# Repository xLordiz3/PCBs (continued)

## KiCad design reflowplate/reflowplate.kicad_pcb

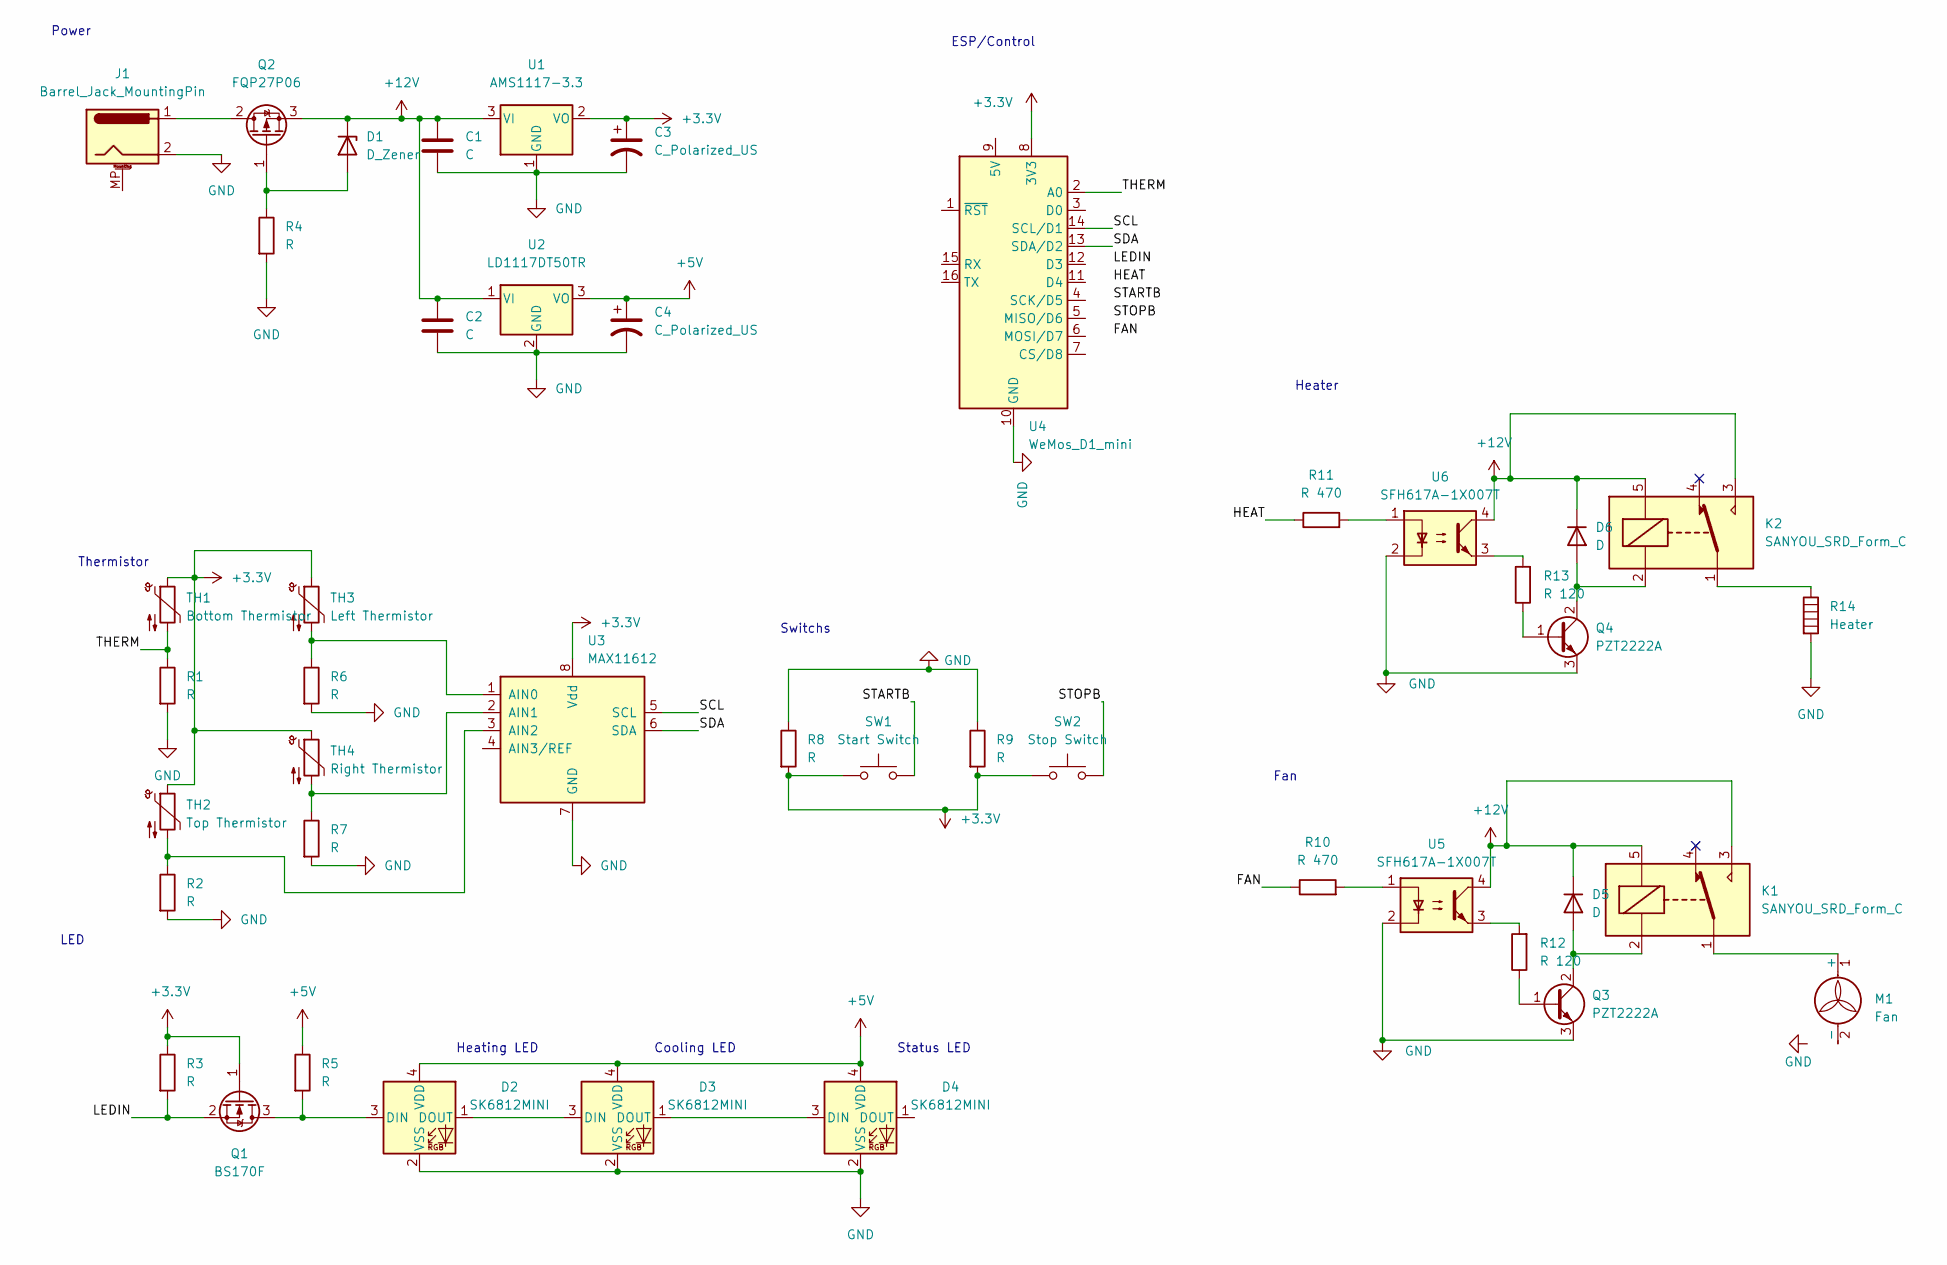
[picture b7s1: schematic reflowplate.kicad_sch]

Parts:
C1, C2: C; CP_EIA-6032-15_Kemet-U_Pad2.25x2.35mm_HandSolder
C3, C4: C_Polarized_US; CP_Elec_5x5.7
D1: D_Zener; D_0805_2012Metric_Pad1.15x1.40mm_HandSolder
D2, D3, D4: SK6812MINI; LED_SK6812MINI_PLCC4_3.5x3.5mm_P1.75mm
D5, D6: D; D_0805_2012Metric_Pad1.15x1.40mm_HandSolder
J1: Barrel_Jack_MountingPin; BarrelJack_Horizontal
K1, K2: SANYOU_SRD_Form_C; Relay_SPDT_SANYOU_SRD_Series_Form_C
M1: Fan; TerminalBlock_Wuerth_691311400102_P7.62mm
Q1: BS170F; SOT-23
Q2: FQP27P06; TO-252-3_TabPin2
Q3, Q4: PZT2222A; SOT-223-3_TabPin2
R1, R2, R3, R4, R5, R6, R7, R8, R9: R; R_0805_2012Metric_Pad1.20x1.40mm_HandSolder
R10, R11: R 470; R_0805_2012Metric_Pad1.20x1.40mm_HandSolder
R12, R13: R 120; R_0805_2012Metric_Pad1.20x1.40mm_HandSolder
R14: Heater; TerminalBlock_Wuerth_691311400102_P7.62mm
SW1: Start Switch; SW_Push_1P1T_NO_6x6mm_H9.5mm
SW2: Stop Switch; SW_Push_1P1T_NO_6x6mm_H9.5mm
TH1: Bottom Thermistor; PinHeader_1x02_P2.54mm_Vertical
TH2: Top Thermistor; PinHeader_1x02_P2.54mm_Vertical
TH3: Left Thermistor; PinHeader_1x02_P2.54mm_Vertical
TH4: Right Thermistor; PinHeader_1x02_P2.54mm_Vertical
U1: AMS1117-3.3; SOT-223-3_TabPin2
U2: LD1117DT50TR; TO-252-2
U3: MAX11612; MSOP-8+SOT23-8
U4: WeMos_D1_mini; WEMOS_D1_mini_light
U5, U6: SFH617A-1X007T; SMDIP-4_W9.53mm_Clearance8mm

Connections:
+3.3V: C3.1, Q1.1 (G), R3.1, R8.2, R9.2, SW1.1, SW2.1, TH1.1, TH2.1, TH3.1, TH4.1, U1.2 (VO), U3.8 (Vdd), U4.8 (3V3)
+5V: C4.1, D2.4 (VDD), D3.4 (VDD), D4.4 (VDD), R5.1, U2.3 (VO)
+12V: C1.1, C2.1, D1.1 (K), D5.1 (K), D6.1 (K), K1.3, K1.5, K2.3, K2.5, Q2.3 (S), U1.3 (VI), U2.1 (VI), U5.4, U6.4
/FAN: R10.1
/HEAT: R11.1
/LEDIN: Q1.2 (S), R3.2
/SCL: U3.5 (SCL), U4.14 (SCL/D1)
/SDA: U3.6 (SDA), U4.13 (SDA/D2)
/STARTB: SW1.2
/STOPB: SW2.2
/THERM: R1.1, TH1.2, U4.2 (A0)
GND: C1.2, C2.2, C3.2, C4.2, D2.2 (VSS), D3.2 (VSS), D4.2 (VSS), J1.2, M1.2 (-), Q3.3 (E), Q4.3 (E), R1.2, R2.2, R4.2, R6.2, R7.2, R8.1, R9.1, R14.2, U1.1 (GND), U2.2 (GND), U3.7 (GND), U4.10 (GND), U5.2, U6.2
unnamed: D1.2 (A), Q2.1 (G), R4.1
unnamed: D2.1 (DOUT), D3.3 (DIN)
unnamed: D2.3 (DIN), Q1.3 (D), R5.2
unnamed: D3.1 (DOUT), D4.3 (DIN)
unnamed: D5.2 (A), K1.2, Q3.2 (C)
unnamed: D6.2 (A), K2.2, Q4.2 (C)
unnamed: J1.1, Q2.2 (D)
unnamed: K1.1, M1.1 (+)
unnamed: K2.1, R14.1
unnamed: Q3.1 (B), R12.1
unnamed: Q4.1 (B), R13.1
unnamed: R2.1, TH2.2, U3.3 (AIN2)
unnamed: R6.1, TH3.2, U3.1 (AIN0)
unnamed: R7.1, TH4.2, U3.2 (AIN1)
unnamed: R10.2, U5.1
unnamed: R11.2, U6.1
unnamed: R12.2, U5.3
unnamed: R13.2, U6.3

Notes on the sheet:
Cooling LED
Switchs
Fan
Status LED
Heating LED
ESP/Control
Heater
LED
Thermistor
Power

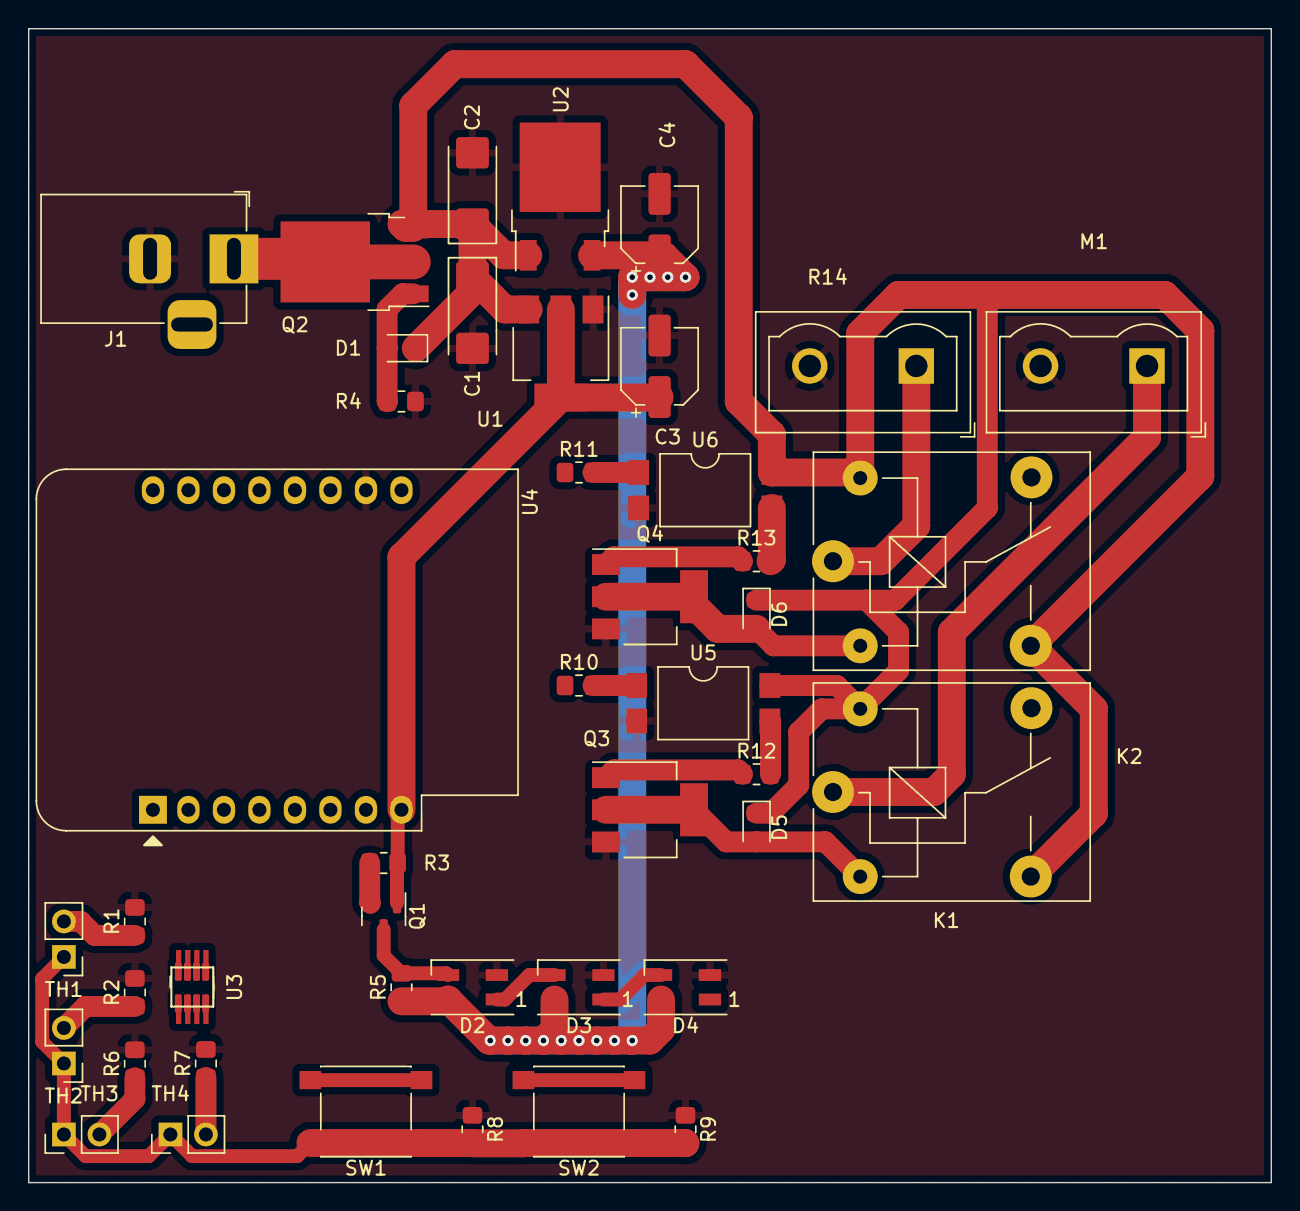
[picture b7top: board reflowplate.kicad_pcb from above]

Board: 2 copper layers, 88.9 x 82.5 mm, 44 parts (0 on the bottom side), 26 nets.

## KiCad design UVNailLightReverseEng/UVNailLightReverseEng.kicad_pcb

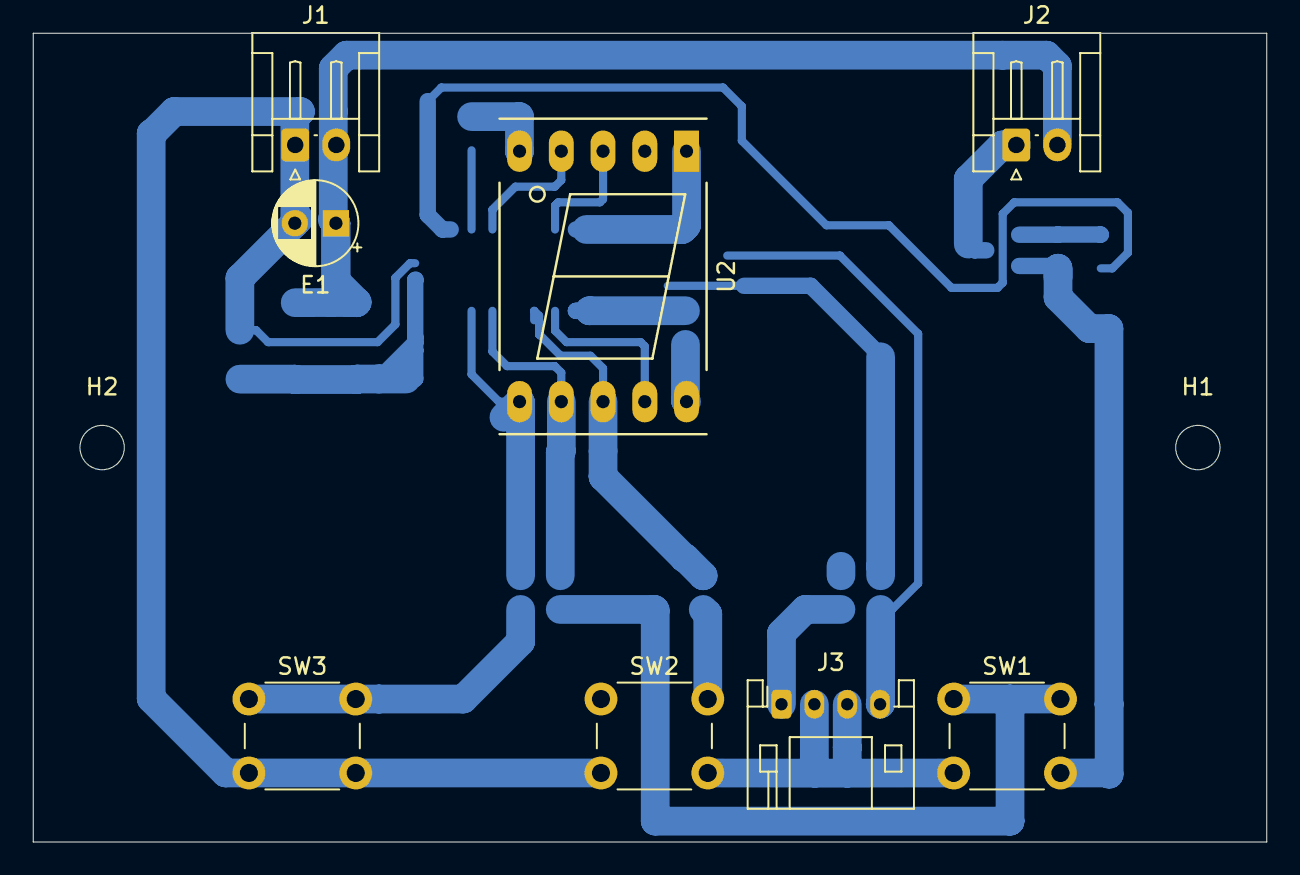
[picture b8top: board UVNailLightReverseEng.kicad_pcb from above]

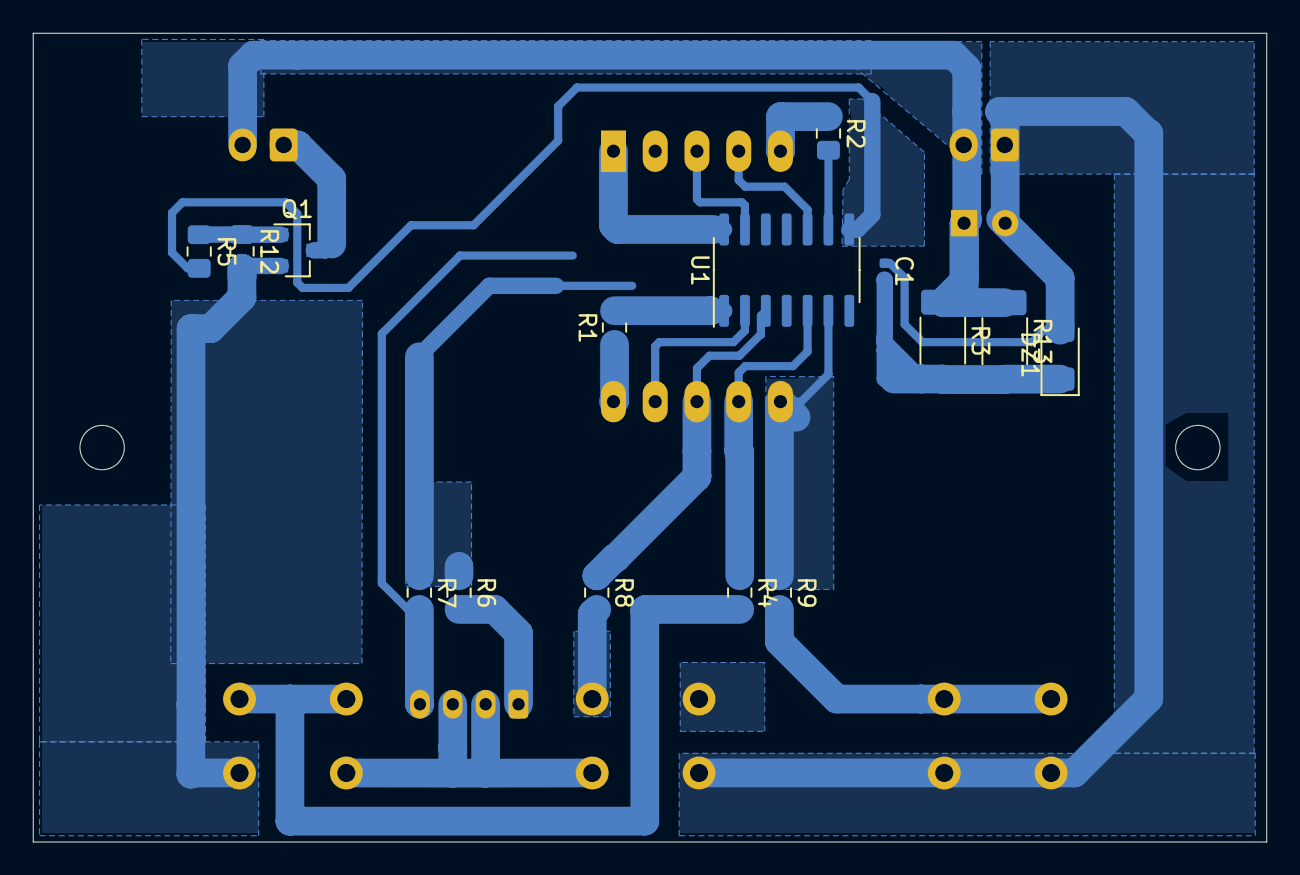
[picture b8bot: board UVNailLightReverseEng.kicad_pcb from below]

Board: 2 copper layers, 75.1 x 49.2 mm, 25 parts (15 on the bottom side), 23 nets.

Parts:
C1: C; C_0402_1005Metric
DZ1: D_Zener; D_1206_3216Metric_Pad1.42x1.75mm_HandSolder
E1: 100 uF; CP_Radial_D5.0mm_P2.50mm
H1, H2: MountingHole; MountingHole_2.7mm_M2.5
J1: Power; JST_EH_S2B-EH_1x02_P2.50mm_Horizontal
J2: LED; JST_EH_S2B-EH_1x02_P2.50mm_Horizontal
J3: IR; JST_PH_S4B-PH-K_1x04_P2.00mm_Horizontal
Q1: IRLML0030; SOT-23
R1, R2: R 330; R_0805_2012Metric_Pad1.15x1.40mm_HandSolder
R3, R13: R 2K; R_2010_5025Metric_Pad1.52x2.65mm_HandSolder
R4, R8, R9: R 2K; R_0805_2012Metric_Pad1.15x1.40mm_HandSolder
R5: R 101; R_0805_2012Metric_Pad1.15x1.40mm_HandSolder
R6: 270; R_0805_2012Metric_Pad1.15x1.40mm_HandSolder
R7: R 15K; R_0805_2012Metric_Pad1.15x1.40mm_HandSolder
R12: R 10K; R_0805_2012Metric_Pad1.15x1.40mm_HandSolder
SW1: 30S; SW_PUSH_6mm
SW2: 60S; SW_PUSH_6mm
SW3: 99S LP; SW_PUSH_6mm
U1: Controller; SOIC-14_3.9x8.7mm_P1.27mm
U2: HDSM-441B; 7SegmentLED_LTS6760_LTS6780

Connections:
GND: C1.1, DZ1.2, E1.2, J1.1, J3.2, J3.3, Q1.2, R12.2, SW1.2, SW2.2, SW3.2
unnamed: C1.2, DZ1.1, R3.2, R13.2
unnamed: J2.1, Q1.3
unnamed: J3.1, R6.2
unnamed: J3.4, R7.2
unnamed: Q1.1, R5.1, R12.1
unnamed: R1.1, U2.10
unnamed: R1.2, U1.1
unnamed: R2.1, U2.5
unnamed: R2.2, U1.9
unnamed: R4.1, U1.5, U2.7
unnamed: R4.2, SW1.1
unnamed: R5.2, U1.8
unnamed: R6.1, R7.1
unnamed: R8.1, U1.3, U2.8
unnamed: R8.2, SW2.1
unnamed: R9.1, U1.6, U2.6
unnamed: R9.2, SW3.1
unnamed: U1.2, U2.9
unnamed: U1.10, U2.4
unnamed: U1.13, U2.3
unnamed: U1.14, U2.1
VCC: E1.1, J1.2, J2.2, R3.1, R13.1
